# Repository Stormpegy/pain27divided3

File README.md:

the pain27 wasn't painful enough, so i turned it in to a split  
look at it, it's beautiful!  

takes a sparkfun promicro (or clone) and 2x 8 pin + 2-3x 2 pin 2.54mm spacing screw terminal blocks, sure you could put some nice headers and custom make a cable, but this way is ~~worse~~ uh,, better  
you'll also need some M2 screws / standoffs and mx style keyswitches of your choice, i recommend gateron as they're some of the cheapest and you'll regret building this board just a little less  
keycaps? maybe  

***Notice***  
I don't actually recommend getting the pcb produced in it's current state, numerous screw holes interfere with switches, the bottom corners of the switches can be clipped and assembled just fine though i'll get to updating it one day  
Q P M and the left hand 2 port screw terminal are the culprits, feel free to space them out more and PR  

[Firmware is here :)](https://github.com/Stormpegy/qmk_firmware/tree/stormpegy/keyboards/stormpegy/pain273) 

[the og meme is here](https://github.com/uuupah/pain27) 

Licensed under CC0

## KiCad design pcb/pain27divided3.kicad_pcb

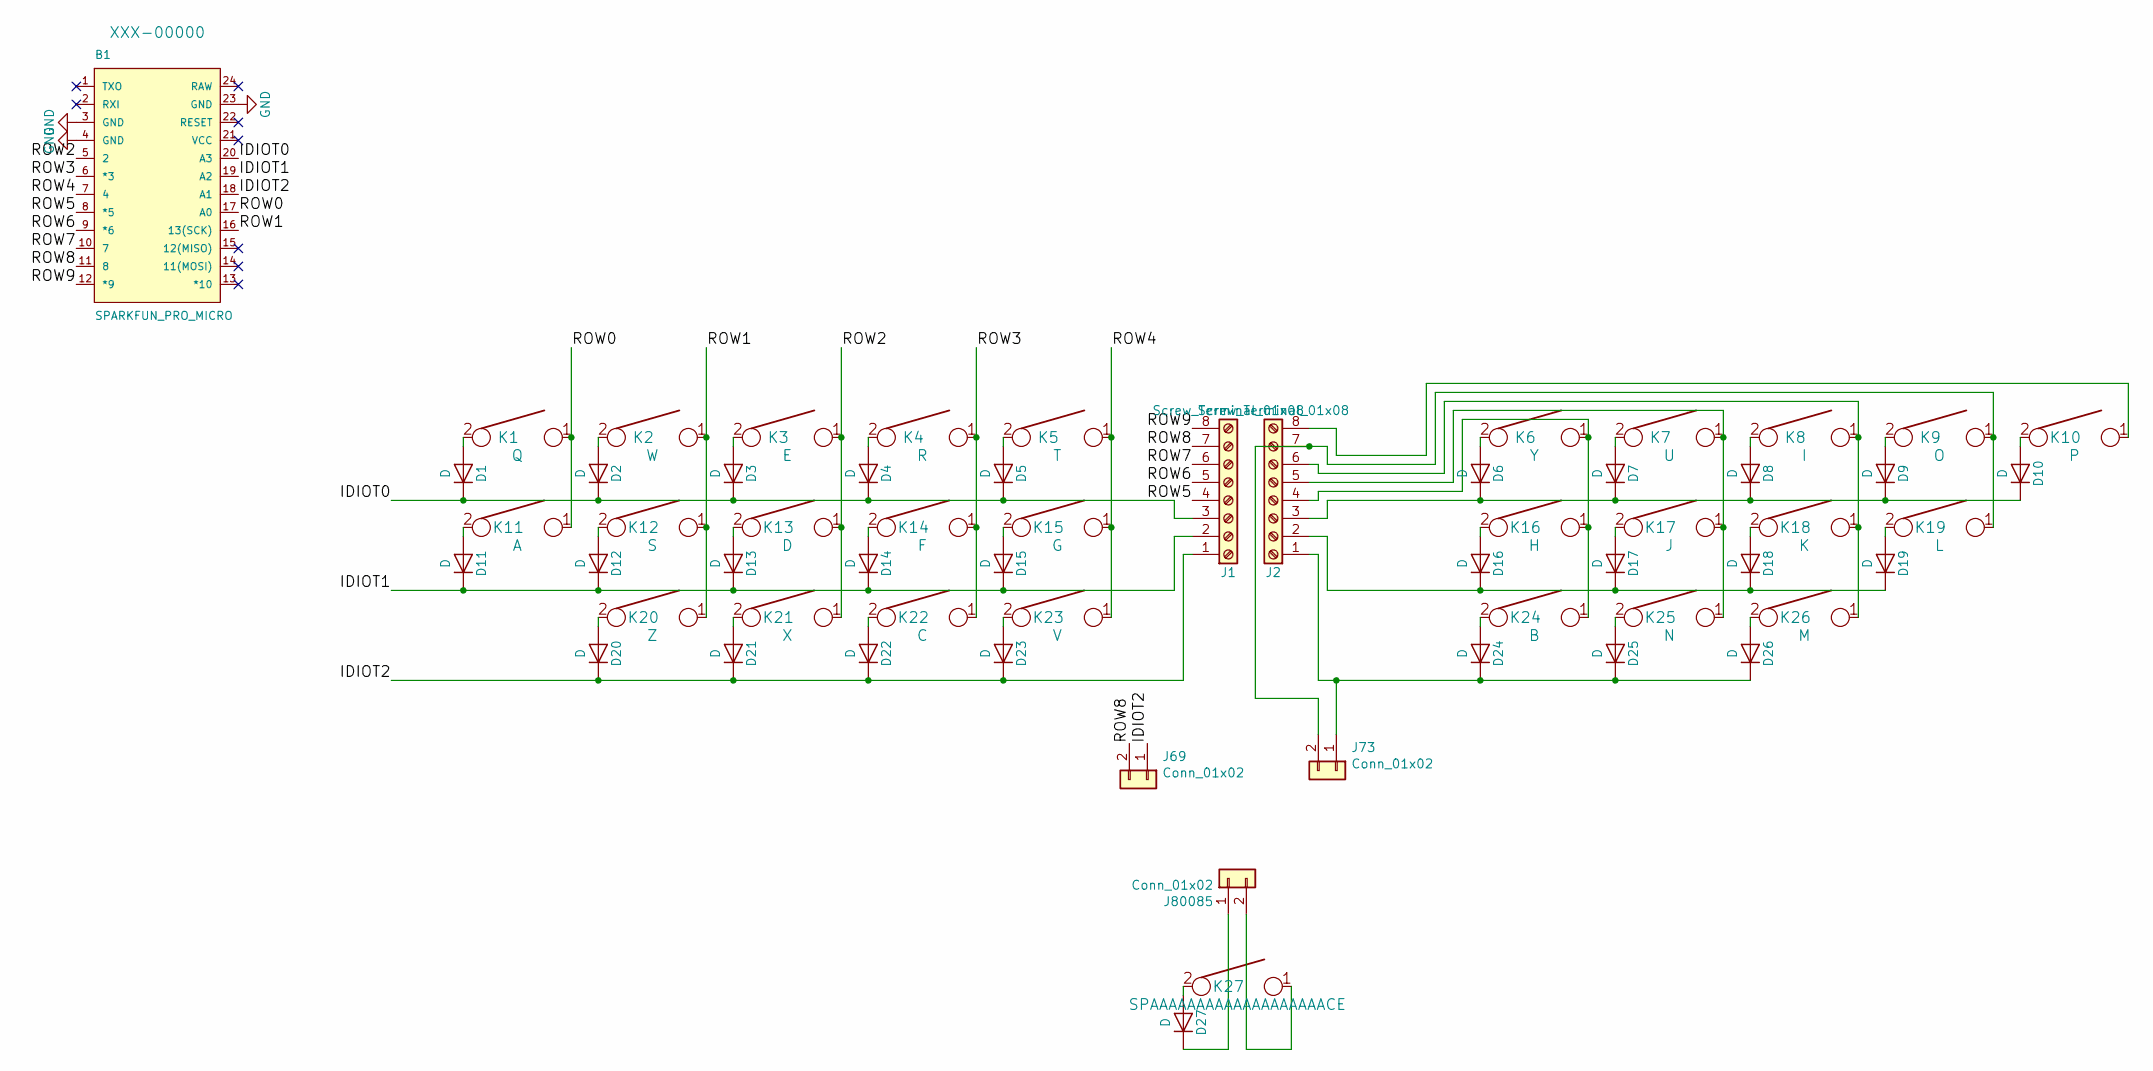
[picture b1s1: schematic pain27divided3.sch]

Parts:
B1: SPARKFUN_PRO_MICRO
D1, D2, D3, D4, D5, D6, D7, D8, D9, D10, D11, D12, D13, D14, D15, D16, D17, D18, D19, D20, D21, D22, D23, D24, D25, D26, D27: D; D_SOD-123
J1, J2: Screw_Terminal_01x08; TerminalBlock_Phoenix_MPT-2.54mm_8pol
J69, J73, J80085: Conn_01x02; Pin_Header_Straight_1x02_Pitch2.54mm
K1: Q; MX_PCB_100H
K2: W; MX_PCB_100H
K3: E; MX_PCB_100H
K4: R; MX_PCB_100H
K5: T; MX_PCB_100H
K6: Y; MX_PCB_100H
K7: U; MX_PCB_100H
K8: I; MX_PCB_100H
K9: O; MX_PCB_100H
K10: P; MX_PCB_100H
K11: A; MX_PCB_100H
K12: S; MX_PCB_100H
K13: D; MX_PCB_100H
K14: F; MX_PCB_100H
K15: G; MX_PCB_100H
K16: H; MX_PCB_100H
K17: J; MX_PCB_100H
K18: K; MX_PCB_100H
K19: L; MX_PCB_100H
K20: Z; MX_PCB_100H
K21: X; MX_PCB_100H
K22: C; MX_PCB_100H
K23: V; MX_PCB_100H
K24: B; MX_PCB_100H
K25: N; MX_PCB_100H
K26: M; MX_PCB_100H
K27: SPAAAAAAAAAAAAAAAAAAACE; MX_PCB_625H

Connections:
/IDIOT0: B1.20 (A3), D1.1 (K), D2.1 (K), D3.1 (K), D4.1 (K), D5.1 (K), J1.3
/IDIOT1: B1.19 (A2), D11.1 (K), D12.1 (K), D13.1 (K), D14.1 (K), D15.1 (K), J1.2
/IDIOT2: B1.18 (A1), D20.1 (K), D21.1 (K), D22.1 (K), D23.1 (K), J1.1, J69.1
/ROW0: B1.17 (A0), K1.1, K11.1
/ROW1: B1.16 (13(SCK)), K2.1, K12.1, K20.1
/ROW2: B1.5 (2), K3.1, K13.1, K21.1
/ROW3: B1.6 (*3), K4.1, K14.1, K22.1
/ROW4: B1.7 (4), K5.1, K15.1, K23.1
/ROW5: B1.8 (*5), J1.4
/ROW6: B1.9 (*6), J1.5
/ROW7: B1.10 (7), J1.6
/ROW8: B1.11 (8), J1.7, J69.2
/ROW9: B1.12 (*9), J1.8
GND: B1.3 (GND), B1.4 (GND), B1.23 (GND)
unnamed: D1.2 (A), K1.2
unnamed: D2.2 (A), K2.2
unnamed: D3.2 (A), K3.2
unnamed: D4.2 (A), K4.2
unnamed: D5.2 (A), K5.2
unnamed: D6.2 (A), K6.2
unnamed: D7.2 (A), K7.2
unnamed: D8.2 (A), K8.2
unnamed: D9.2 (A), K9.2
unnamed: D6.1 (K), D7.1 (K), D8.1 (K), D9.1 (K), D10.1 (K), J2.3
unnamed: D10.2 (A), K10.2
unnamed: D11.2 (A), K11.2
unnamed: D12.2 (A), K12.2
unnamed: D13.2 (A), K13.2
unnamed: D14.2 (A), K14.2
unnamed: D15.2 (A), K15.2
unnamed: D16.1 (K), D17.1 (K), D18.1 (K), D19.1 (K), J2.2
unnamed: D16.2 (A), K16.2
unnamed: D17.2 (A), K17.2
unnamed: D18.2 (A), K18.2
unnamed: D19.2 (A), K19.2
unnamed: D20.2 (A), K20.2
unnamed: D21.2 (A), K21.2
unnamed: D22.2 (A), K22.2
unnamed: D23.2 (A), K23.2
unnamed: D24.1 (K), D25.1 (K), D26.1 (K), J2.1, J73.1
unnamed: D24.2 (A), K24.2
unnamed: D25.2 (A), K25.2
unnamed: D26.2 (A), K26.2
unnamed: D27.1 (K), J80085.1
unnamed: D27.2 (A), K27.2
unnamed: J2.4, K6.1, K16.1, K24.1
unnamed: J2.5, K7.1, K17.1, K25.1
unnamed: J2.6, K8.1, K18.1, K26.1
unnamed: J2.7, J73.2, K9.1, K19.1
unnamed: J2.8, K10.1
unnamed: J80085.2, K27.1

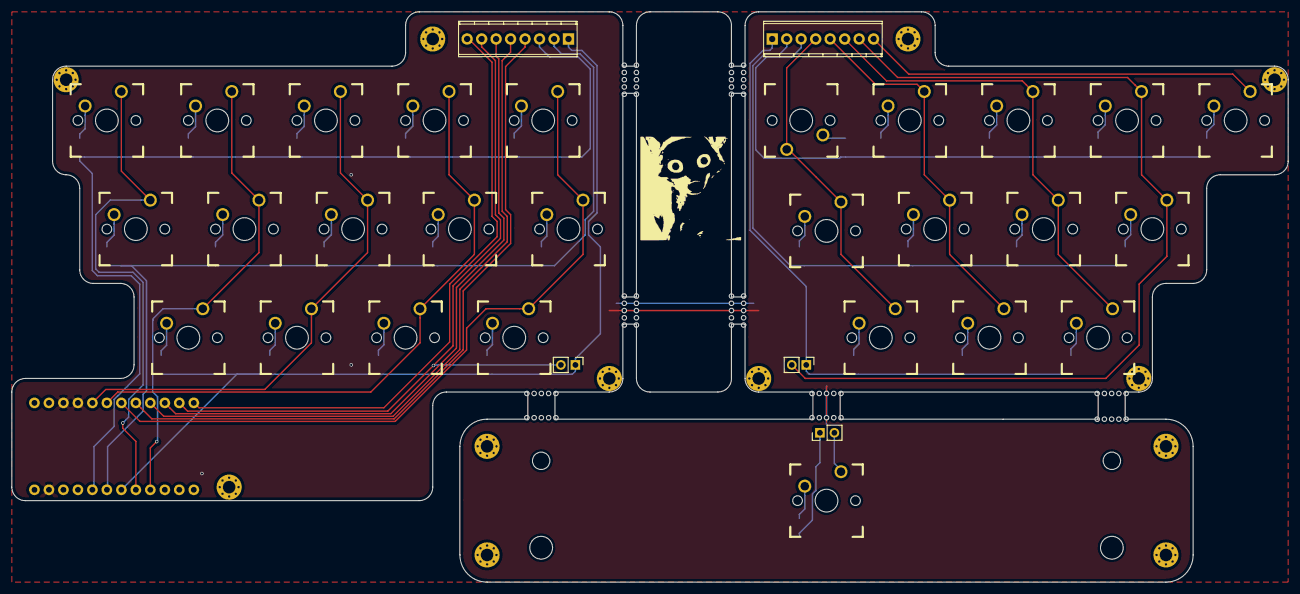
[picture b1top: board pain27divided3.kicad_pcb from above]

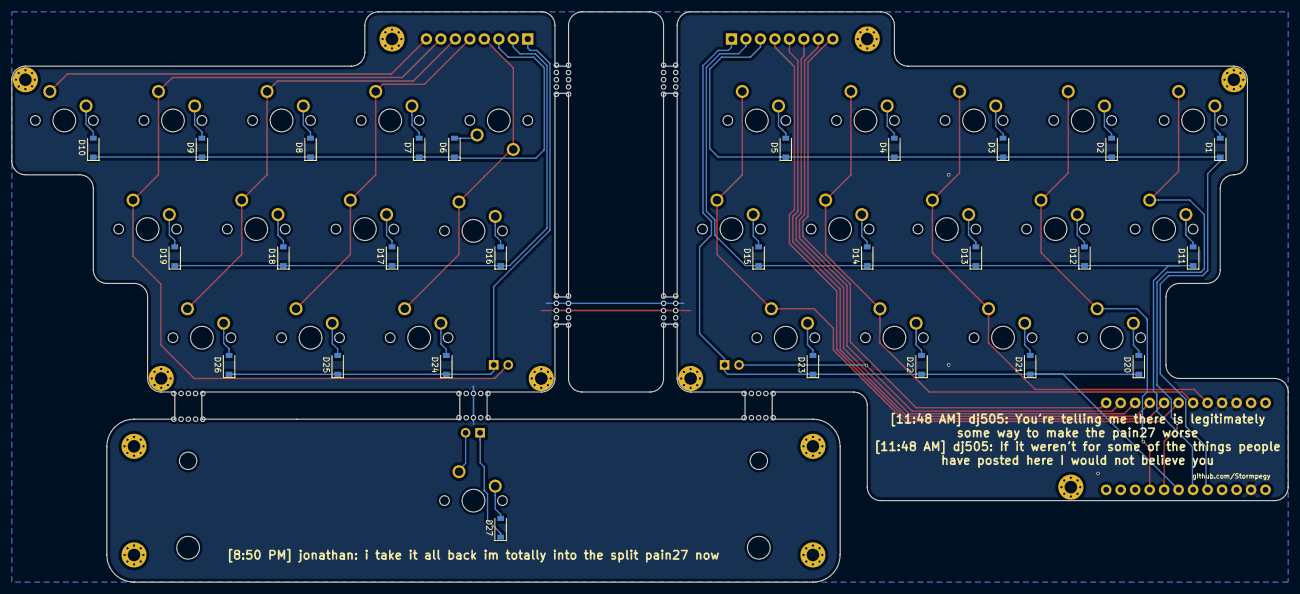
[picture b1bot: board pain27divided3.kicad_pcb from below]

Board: 2 copper layers, 223.8 x 100.0 mm, 60 parts (28 on the bottom side), 51 nets.

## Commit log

2021-04-22 added github url to pcb
    its ready
2021-04-23 read me maybe?
2021-04-24 isn't it pretty
2021-11-02 just a little housekeeping
